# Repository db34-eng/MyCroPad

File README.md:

# MyCroPad-
A 9-key matrix with a rotary encoder and an OLED screen, created for gaming.

### PCB

### Case

Check out my PCB & try it out here:
https://kicanvas.org/?repo=https%3A%2F%2Fgithub.com%2Fdb34-eng%2FMyCroPad-

Check out my case here: 
https://autode.sk/452PsHg

## Features-
- A 3x3 9x Key Matrix
- 1x OLED Screen
- 1x Rotary Encoder Switch
- All controlled by a XIAO Seeed Studio Seeeduino
- Designed for gaming, OLED screen provides visual feedback for buttons pressed, and Rotary Encoder provides finer control over movement.
- All on a custom, designed by me, PCB (linked above)
- A 3d printed case
- Running on custom designed QMK firmware

## How it works- 
- 9 key inputs & 2 directions from Rotary Encoder travel through PCB to the Seeeduino, which sends the signal to the connected computer, and shows an animation on the OLED screen. 
- Will be updated once QMK firmware is completed

## How to do it yourself:
- If you want to copy my design, go ahead, as long as you follow the rules in License.
1. Download all files in this repository (IT IS NOT COMPLETE YET. THIS WILL BE UPDATED AND REMOVED IN THE FUTURE(QMK FILES NOT COMPLETED))
2. Get your parts - Get all the parts in the Bill Of Materials
3. 3d Print the case - Use the STEP file and a STEP File Converter (found on google) to change it to the file type your computer uses OR if you have Fusion, open the Fusion file and click File -> Export and choose the file type needed.
4. Manufacture the PCB - Grab the PCB files, boot up KiCad, and edit them if desired. Then, when in the PCB viewer, click File -> Fabrication Outputs -> and choose your desired file type. Then, upload this file to a PCB manufacturer of your choice. (Costs money btw $$$)
5. Assemble the unit
6. Use the QMK firmware to make the keyboard work
7. Have fun with your new MacroPad!!!

## Credits-
Thanks to everyone in the #hackpad slack for helping answer my many questions and teaching me when I didn't understand. Specific thank-yous to:
- ### Pixelated Carlisle
- ### arthihalder
- ### CharlieCatMeow
- ### mountnrocky
- ### hww
- ### yassin
- ### dominic.stange13
- ### codecraft07
Thank you all for your help, I couldn't have done it without you!
Also, this project was created for the Stardance challenge. Check it out here:
https://stardance.hackclub.com/home

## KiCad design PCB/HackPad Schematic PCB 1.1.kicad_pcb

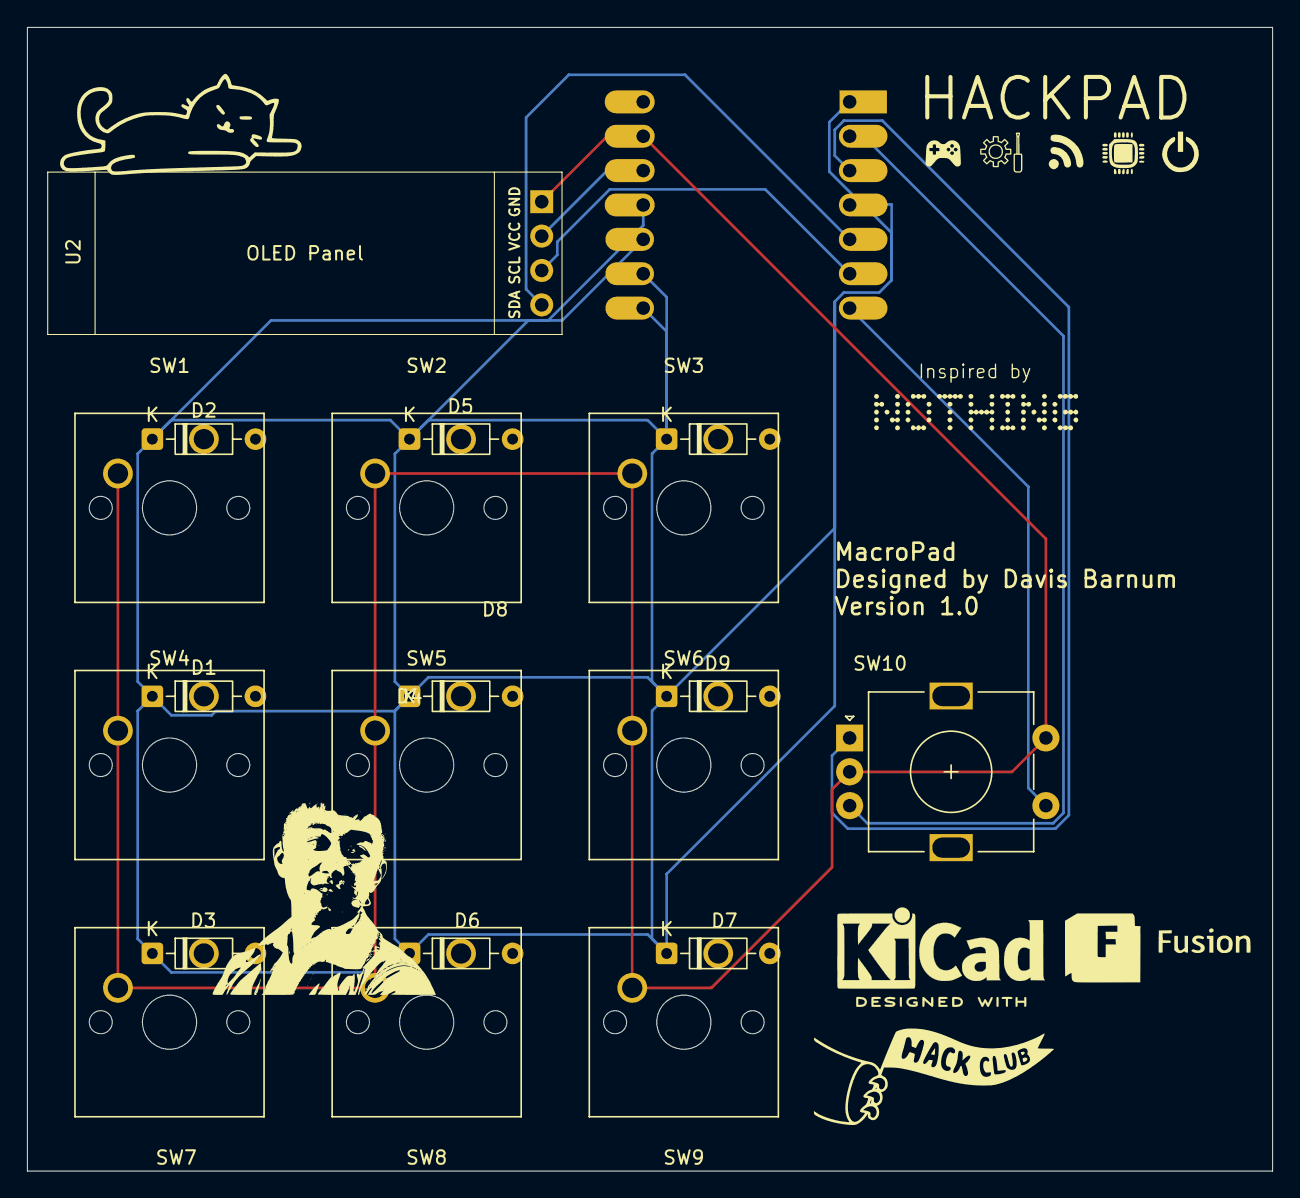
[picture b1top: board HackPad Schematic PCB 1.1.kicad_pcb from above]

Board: 2 copper layers, 92.0 x 84.5 mm, 21 parts (1 on the bottom side), 17 nets.

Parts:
D1, D2, D3, D4, D5, D6, D7, D8, D9: 1N4148; D_DO-35_SOD27_P7.62mm_Horizontal
SW1, SW2, SW3, SW4, SW5, SW6, SW7, SW8, SW9: SW_Push; SW_Cherry_MX_1.00u_PCB
SW10: RotaryEncoder_Switch; RotaryEncoder_Alps_EC11E-Switch_Vertical_H20mm
U1: MOUDLE-SEEEDUINO-XIAO; XIAO-Generic-Hybrid-14P-2.54-21X17.8MM
U2: ER_OLEDM0.91_1x-I2C; SSD1306-0.91-OLED-4pin-128x32

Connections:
GND: SW1.2, SW2.2, SW3.2, SW4.2, SW5.2, SW6.2, SW7.2, SW8.2, SW9.2, SW10.C, SW10.S2, U1.13 (GND), U2.1 (GND)
unnamed: D1.2 (A), SW4.1
unnamed: D1.1 (K), D2.1 (K), D3.1 (K), D4.1 (K), D5.1 (K), D6.1 (K), D7.1 (K), D8.1 (K), D9.1 (K), U1.1 (PA02_A0_D0), U1.4 (PA11_A3_D3), U1.8 (PB09_A7_D7_RX), U1.9 (PA7_A8_D8_SCK), U1.10 (PA5_A9_D9_MISO), U1.11 (PA6_A10_D10_MOSI)
unnamed: D2.2 (A), SW1.1
unnamed: D3.2 (A), SW7.1
unnamed: D4.2 (A), SW5.1
unnamed: D5.2 (A), SW2.1
unnamed: D6.2 (A), SW8.1
unnamed: D7.2 (A), SW9.1
unnamed: D8.2 (A), SW3.1
unnamed: D9.2 (A), SW6.1
unnamed: U1.12 (3V3), U2.2 (VCC)
unnamed: SW10.B, U1.2 (PA4_A1_D1)
unnamed: U1.5 (PA8_A4_D4_SDA), U2.4 (SDA)
unnamed: U1.6 (PA9_A5_D5_SCL), U2.3 (SCL)
unnamed: SW10.A, U1.3 (PA10_A2_D2)
unnamed: SW10.S1, U1.7 (PB08_A6_D6_TX)
